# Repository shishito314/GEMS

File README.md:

# GEMS - Glovebox Environmental Monitoring System

## Table of Contents

- [Overview](#overview)
- [Instructions For Use](#instructions-for-use)
  - [Changing Display I2C Addresses](#changing-display-i2c-addresses)
  - [Binding Arduino MAC Addresses](#binding-arduino-mac-addresses)
  - [Python Configuration](#python-configuration)
  - [Adding Sensors](#adding-sensors)
  - [Changing Program Constants and Parameters](#changing-program-constants-and-parameters)
- [How GEMS works](#how-gems-works)
  - [Hardware](#hardware)
    - [Bill Of Materials](https://docs.google.com/spreadsheets/d/1ikpGfJ6LjHaBAVGgCHs3OJ50SzMK_VNal6e07bsFQgU/edit?usp=sharing)
    - [Wifi Communications](#wifi-communications)
    - [Sensor Measurement](#sensor-measurement)
  - [Software](#software)
    - [Python Overview](#python-overview)
    - [Arduino Code Overview](#arduino-code-overview)
    - [Technical Details](#technical-details)
      - [Wifi & Caching](#wifi--caching)
      - [Smoothing](#smoothing)
      - [Behavior on Disconnect](#behavior-on-disconnect)
- [Known Issues and Limitations](#known-issues-and-limitations)
- [Links](#links)

## Overview

Here's the basic idea of the GEMS system in it's current implementation:

There are two arduino boards, one inside and one outside the glovebox. The one inside is optional and connects to a temperature sensor. The one outside is part of a unit that connects to an oxygen sensor, a water/humidity sensor, and three displays (one to display each sensor measurement).

When the loop.py program is run on a computer connected to the GEMS router network, it will periodically send HTTP requests to the arduinos, which are effectively hosting servers. When it sends the request, the arduino will respond with the current sensor measurement (in the form of an HTML webpage). When it gets the measurements, the computer will log them in a file.

Then, with the current measurements, the computer will decide what should be displayed. With another HTTP request, it will send that information to the arduino with the displays, which will update the displays accordingly. Then, on the next cycle, the computer will run that entire process again, and so on.

## Instructions For Use

Here are instructions for the full setup process:

1. Install desired sensors on glovebox
2. Connect computer to router network with USB Wifi adapter (here using an auxiliary wifi adapter to retain internet access, since the local router isn't connected to the internet). You may need to install the driver from the [TP-Link download center](https://www.tp-link.com/us/support/download/) (T3U Plus is the device).
3. Set up router in lab with the given instructions. (No need for WAN/Internet, so you can skip it). Make sure router is on and network is available.
4. Optionally, install [git](https://git-scm.com/install/) on the lab computer. This will allow for easier updates if changes are made to the GEMS github.
5. If using git, clone the GEMS repository into the preferred filesystem location. On Mac and Windows, You can use the commands `cd your_folder_path` and then `git clone https://github.com/shishito314/GEMS.git`. You may need to sign in to your github.
6. If not using git, you can download the repository manually (e.g. via zip)
7. Install [Python](https://www.python.org/downloads/) on lab computer (the latest stable (non pre-release) version of Python 3 should work) You can verify that the install worked by running `python --version` in the command line.
8. Acquire or construct physical GEMS unit with arduino, PCB, displays, and box. You will need:
   - PCB soldered with all components
   - Displays soldered together ([Adafruit guide here](https://learn.adafruit.com/adafruit-7-segment-led-featherwings/overview))
   - Displays soldered with correct I2C addresses ([explanation here](#changing-display-i2c-addresses))
   - Displays plugged into header pins on PCB
   - Arduino connected to header pins on PCB
   - Box screwed together
9. Install [Arduino IDE](https://www.arduino.cc/en/software/), either on a personal or lab computer. It's only needed for setup to upload code to the arduinos.
10. Within Arduino IDE, go to the board manager and install the package for arduino megaAVR boards (like the Uno Wifi Rev2)
11. Using the Library manager, install WiFiNINA and the Adafruit LED Backpack library, including all dependencies.
12. Open the desired arduino sketch (.ino) in Arduino IDE and go to config.h. Edit NETWORK_SSID and NETWORK_PASS to be correct for the room router. Save the file.
13. Upload the code using a printer cable (USB-B) with data capability (some only transmit power). When you plug in the arduino, click the dropdown in the top left and select the board, then click upload (right arrow icon). If the arduino doesn't appear in the dropdown, there's a chance that the cable doesn't transmit data or that you need to cycle power to the arduino.
14. With arduino plugged in, open (or close and reopen) the serial monitor with the button in the top right to verify that it's working. You should see a couple prints to the serial monitor and after ~10s, the arduino should connect to the router and print out the IP address it was assigned.
15. Keeping the arduino plugged in (so we know the current IP address), bind the arduino MAC Address to the desired IP Address ([guide here](#binding-arduino-mac-adresses))
16. Restart arduino (you can close and reopen the serial monitor) and verify that it gets the desired IP address after network connection.
17. Connect the GEMS unit to the sensors via screw terminals and leads. Then using the wall mounted power adapter, plug in the PCB (not the arduino) to power. The PCB barrel jack is on the left side of the box, and the arduino's barrel jack (which can't handle this voltage) is on the top. Turn the unit on with the rocker switch (on = left down). The displays should come on after a few seconds.
18. On the lab computer, go to the command line and run `pip install matplotlib`. Alternatively you can use the environment.yml file and conda if you have it installed (otherwise probably overkill).
19. Edit the config.txt file in the Python subfolder. ([guide here](#python-configuration))
20. Run loop.py by double clicking in the file explorer or from the command line. If the program is successful, you should see a glovebox-named folder with sensor data pop up in the Python subfolder after a little while.
21. After you get some data, you can check on it by running gui.py
22. For optional temperature support, plug in a thermocouple to an arduino and go through a similar process to the other arduino:
    - Download the Adafruit MAX6675 Library and upload the temperature sketch to the arduino (again need to change network info in config.h).
    - Bind the arduino MAC Address to the desired IP address
    - Edit config.txt in the python subfolder to account for the temperature arduino
    - After changing config.txt, rerun loop.py to apply changes.
23. You're all set! Thanks for using GEMS.

### Changing Display I2C Addresses

The seven segment displays communicate with the arduino via the I2C protocol, which requires each device to have a unique address. Luckily, we can change the address from the default 0x70 by soldering on the display board.

There are 3 address jumpers on the display board (the pairs of solder pads marked A0, A1, A2). Each jumper represents a bit: 1, 2, and 4 for A0, A1, and A2 respectively. The final address is 0x70 + the sum of all the bits. For example, to get the address 0x73, you would solder together the A0 pads and A1 pads (70 + 1 + 2 = 73).

You can find the Adafruit guide on changing the I2C addresses [here](https://learn.adafruit.com/adafruit-7-segment-led-featherwings/pinouts#changing-addresses-1805676)

In the current GEMS arduino code, the displays are set up as follows:

- Temperature display → 0x70 (no jumpers)
- Oxygen display → 0x71 (A0 soldered)
- Water display → 0x72 (A1 soldered)

### Binding Arduino MAC Adresses

1. Connect to the router network and go to the configuration page at [http://tplinkwifi.net/](http://tplinkwifi.net/) (Note the http, not https). If your computer is connected to internet, you may need to try searching the router IP address directly (solution 2).
2. Sign in with admin password posted on the router
3. Depending on how old your router is, there are different versions of the web page. Either:
   1. Click "Advanced," "Network," and "DHCP Server" (new version)
   2. Click "DHCP" on the left, then "Address Reservation" (old version)
4. With the new version of the webpage, you should be able to scroll down and see the currently connected clients. If you know the IP address of the arduino from the serial monitor output, you can use that to identify its MAC address.
5. Alternatively, you can get the arduino MAC address by temporarily uploading the getMacAddress sketch and reading the output from the serial monitor. You'll need to change the "ssid" and "pass" in the code to the network name and password. WARNING: depending on your library version, the printed MAC address might actually have the pairs of letters/numbers backwards (e.g. AB:CD:EF:12:34:56 is actually 56:34:12:EF:CD:AB).
6. Add a new address reservation line on the router configuration page, and input the MAC Address with the desired IP Address. You can use `198.162.0.11_` as a possible naming scheme, just varying the last digit.
7. If on the old web page, switch address reservation to "Enable"

### Python Configuration

To configure the software for certain gloveboxes, arduinos, and sensors, use the config.txt file in the Python subfolder. If you downloaded or cloned the GEMS repository, an example is provided by default.
Here's the format for a config file:

```
Glovebox: [Name]
Arduino: IP: [IP Adress] Display: [True/False] Sensors: [Sensor1 Sensor2...]
Arduino: IP: [IP Adress] Display: [True/False] Sensors: [Sensor1 Sensor2...]
Glovebox: [Name]
[Arduinos...]
...
```

Here's an example of a config file following that format:

```
Glovebox: pluto
Arduino: IP: 192.168.0.110 Display: True Sensors: Oxy Water
Arduino: IP: 192.168.0.111 Display: False Sensors: Temp
Glovebox: neptune
Arduino: IP: 192.168.0.112 Display: True Sensors: Oxy
Arduino: IP: 192.168.0.113 Display: False Sensors: Temp
```

IMPORTANT: Capitalization and the colons after words are mandatory.

### Adding Sensors:

This section is for adding new sensor types in software (e.g. if you wanted to add functionality for a pressure sensor). Each sensor has a class in gems.py extended from the base Sensor class. To create your own, make a class extended from the base Sensor class and define the addVal and getLog methods for your sensor. It might look something like the following:

```python
class NewSensor(Sensor):
  flag = NEW_SENSOR_FLAG # Flag to be used in HTTP communications and logging
  datatype = float # The datatype of the sensor measurements (e.g. float)

  def __init__(self):
    super().__init__()
    self.lastValue = None

  def getLog(self):
    try:
      return str(round(self.lastValue, 3))
    except:
      try:
        return self.lastValue
      except:
        return "Error"

  def getDisplay(self):
    try:
      return str(round(self.lastValue, 3))
    except:
      if (self.lastValue):
        return self.lastValue
      else:
        return DISPLAY_ERROR_MESSAGE

  def addVal(self, val, time):
    self.lastValue = val
```

You can also look at the sensor classes already implemented for some examples.

After making the sensor, class, add a corresponding configuration flag and sensor class to the "SENSOR_CONFIG_FLAG_TO_CLASS" dictionary in the "Set Up Class Instances From Config" section of gems.py. You'll also need to define a flag, (whatever you'd put in place of "NEW_SENSOR_FLAG" in the above example), and add that flag to the LOG_FLAGS list in the constants section of gems.py. It'll get used for parsing through log files with the data utilities.

### Changing Program Constants and Parameters

When changing constants in the programs, it is important to note that variables labeled "MUST MATCH ARDUINO" or "MUST MATCH PYTHON" must be the same in both programs. They should be at the top of gems.py or in the config.h file in the arduino sketches.

## How GEMS works

### Hardware

[Bill Of Materials]([https://docs.google.com/spreadsheets/d/1ikpGfJ6LjHaBAVGgCHs3OJ50SzMK_VNal6e07bsFQgU/edit?usp=sharing])

#### Wifi Communications

Uses:

- Computer with python 3
- Router
- Wifi adapter
- Arduinos

The wifi adapter connects the computer to the router network, and the router network connects the computer and arduinos together. The arduinos are hosting a server, which the computer can send a request to by sending it to "http://" followed by the arduino IP address. The arduinos must have an IP address that doesn't change, so we use the MAC address binding on the router to keep the IP address constant.

#### Sensor Measurement

The oxygen and moisture sensors are 4-20 milliamp loop sensors, with a power lead (24V) and an output (goes across a resistor to GND) The sensor regulates the current on the output to be between 4 and 20 milliamps, and the current corresponds to the sensor measurement.

Since the arduinos can't measure current directly, we instead measure the voltage drop across a known resistor and calculate the current

Since it is important to know the resistance of the resistor accurately, there is a 0.1% tolerance resistor with 25ppm per degree C temperature coefficient.

There are some other pieces of hardware that address a few problems:

- Capacitor: There is a 10 uF capacitor running in parrallel with the resistor. It acts as a low pass filter to reduce some of the noise (15.5KHz sine wave) that had been a prior issue
- Voltage Reference: The built in arduino voltage references weren't accurate enough for the desired specs, so we use an external 4.5V reference.

### Software

#### Python Overview

- [loop.py](./Python/loop.py): The update loop that sends http requests and logs data. It's an infinite loop that must be stopped by closing the python terminal.
- [gems.py](./Python/gems.py): All the architecture and setup for the GEMS system. Parses config.txt upon import.
- [data.py](./Python/data.py): Utility functions for extracting and plotting data from GEMS log files.
- [gui.py](./Python/gui.py): Runs the GEMS GUI (graphical user interface). You can use it to check up on the GEMS system and measurements.

#### Arduino Code Overview

- [oxyWaterDisplay](./Arduino/oxyWaterDisplay/): Handles sensor measurements for the oxygen and dewpoint sensors, wifi communication, and readouts.
- [temp](./Arduino/temp/): Similar to the oxyWaterDisplay sketch, but stripped down for only the temperature sensor and wifi, no displays.
- [getMacAddress.ino](./Arduino/getMacAddress.ino): Connects to the router wifi network, then prints the arduino MAC address in the Serial Monitor.

#### Technical Details

##### Wifi & Caching

The following wifi protocol and caching system are designed to prevent data from being lost, even if HTTP requests or responses are missed:

The arduino has a cache that stores the logs to send to the lab computer. Conceptually, the arduino cache has two parts. The "old" part of the cache consists of data that has already been sent, but the arduino isn't sure that the computer received it. The "new" part of the cache is data that has not yet been sent. (In practice, for memory management, I use an array with flexible start/end indices and wraparound behavior).

Every [CACHE_CYCLE_DELAY] milliseconds, the arduino will add a new log to the new part of the cache. When the arduino receives a request from the lab computer, the request comes with a note that says whether or not the computer got the previous request. If so, the arduino will clear the old cache to avoid sending repeat data. Then, the arduino will send the cache via wifi to the computer, and the entire cache will be labeled as "old" (since the data was sent). If the computer did not receive the previous request, the old cache will not be cleared and therefore the data will be resent.

However, it is still possible that repeat data will be sent, for example if the python program is stopped and restarted. The python program will have written the data in the file, but whether it received the last request defaults to "no" on startup. Therefore, on the first request, the python program won't tell the arduino to clear the old cache, and the old cache will be sent again as a repeat log.

A timestamp system is there to prevent this log duplication. Every log that the arduino makes is labeled with the arduino clock value (in milliseconds) at the time of measurement. When the computer receives the logs, it will save the timestamps of those logs inside a hidden file that persists after the python program is stopped. The next time that the computer gets logs, it will check to make sure that the timestamps for those logs do not line up with the ones in the hidden file. That way, the computer can avoid both missing data and repeating measurements in the log files.

##### Smoothing

Currently, the arduino takes measurements from the analog pins every loop cycle. It adds those measurements to an array for smoothing, and gets rid of the oldest measurement in the array. However, those measurements are not a single reading from the analog pin, but rather many readings averaged out to a single value. That way, a higher smoothing value could be achieved with the same amount of memory than by taking single measurements.

For example, with 30 16-byte-integers worth of memory, you could either have an array with 30 measurements, or you could have an array of 15 averages of 15 measurements each. Therefore, the effective smoothing is with 225 values, not just 30.

Also, the readings can be taken close together, since they are taken right after each other instead of waiting for another cycle of the arduino loop function.

##### Behavior on Disconnect

When the display arduino gets disconnected, it will calculate the oxygen and humidity values locally and display those. It won't display the temperature, instead showing "dISC" for disconnected. It will keep caching new data for when it reconnects, though.

## Known Issues and Limitations

- The arduino clock isn't perfectly accurate, so after a while there may be slightly more or less logs than expected
- Arduino timestamps leave minuscule probability of missing or repeating a log
- Can't support multiple sensors of the same type on one glovebox (because it can't differentiate flags)
- Logging untested with daylight savings time
- Non-flexible file structure
- Some computers may stop sending wifi requests when the computer screen turns off
- No timeout in arduino sketch if client doesn't disconnect

## Links

[Google Drive Folder](https://drive.google.com/drive/folders/1qjnQDnakjW4T2VA_t_dMa19qW6lmA9qH?usp=sharing)

[Full Bill Of Materials](https://docs.google.com/spreadsheets/d/1ikpGfJ6LjHaBAVGgCHs3OJ50SzMK_VNal6e07bsFQgU/edit?usp=sharing)

[Desmos Graph For Spec Calculations](https://www.desmos.com/calculator/oaaztaypr6)

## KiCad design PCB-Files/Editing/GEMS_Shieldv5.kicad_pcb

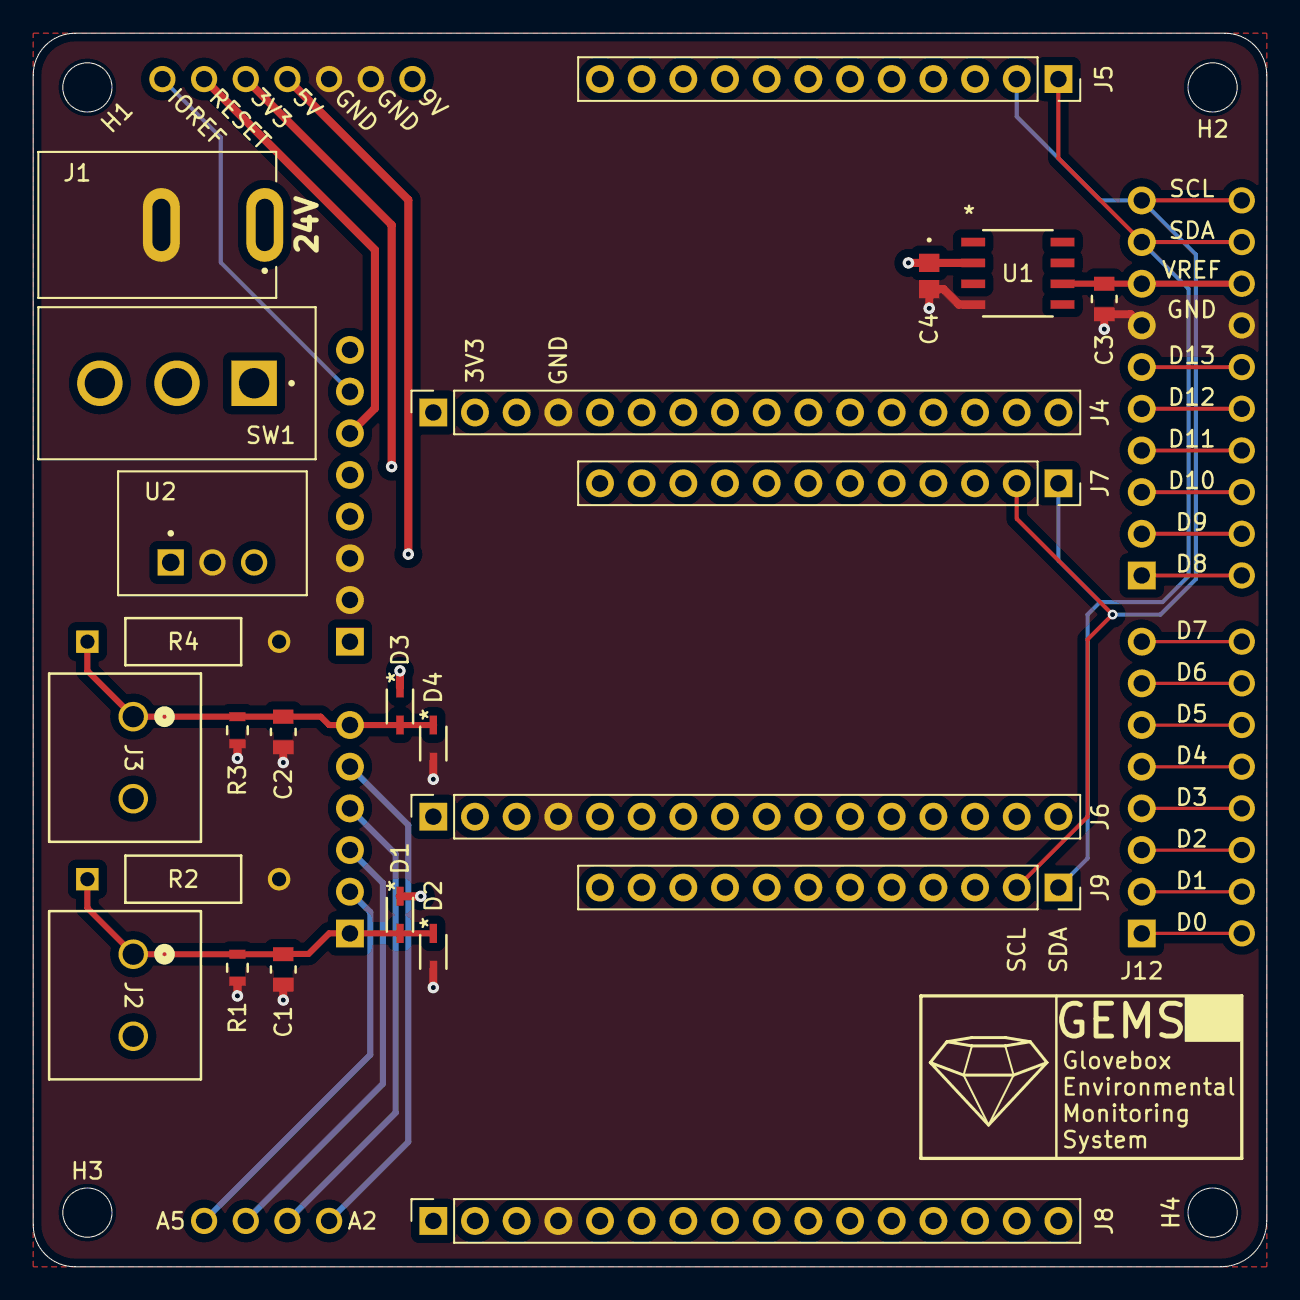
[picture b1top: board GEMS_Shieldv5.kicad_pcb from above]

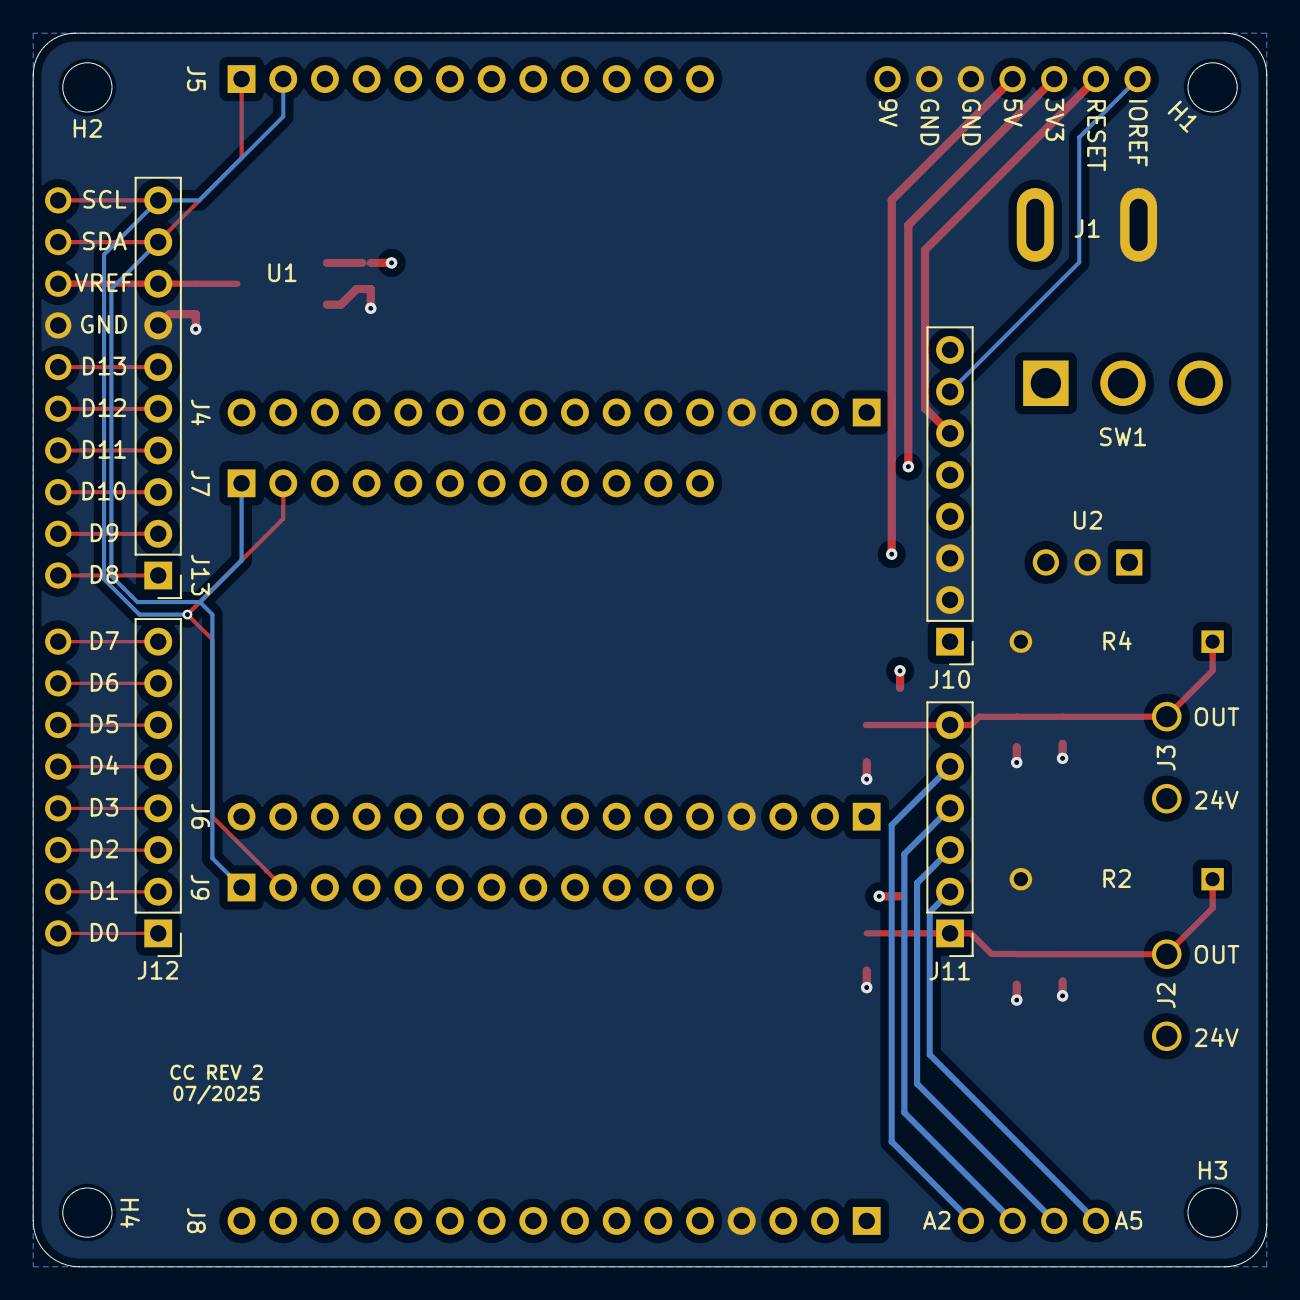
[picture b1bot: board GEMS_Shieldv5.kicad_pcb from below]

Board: 4 copper layers, 75.2 x 75.2 mm, 61 parts (4 on the bottom side), 10 nets.

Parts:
A1: Arduino_UNO_R3; Arduino_Wifi_Drawing
C1, C2: C; CL21A106KOQNNNE_10uF
C3: C; CL21B105KBFNNNE_1uF
C4: C; CAP_KGM21_KAV
D1, D2, D3, D4: D; CR_SOD323_MCC
H1, H2, H3, H4: MountingHole
J1: Barrel_Jack; CUI_PJ-037A
J2, J3: Screw_Terminal_01x02; CONN_1935161_PXC
J4, J6, J8: Conn_01x16_Socket; PinSocket_1x16_P2.54mm_Vertical
J5, J7, J9: Conn_01x12_Socket; PinSocket_1x12_P2.54mm_Vertical
J10, J12: Conn_01x08_Pin; PinHeader_1x08_P2.54mm_Vertical
J11: Conn_01x06_Pin; PinHeader_1x06_P2.54mm_Vertical
J13: Conn_01x10_Pin; PinHeader_1x10_P2.54mm_Vertical
J14, J15, J16, J17, J18, J19, J20, J21, J22, J23, J24, J25, J26, J27, J28, J29, J30, J31, J32, J34, J35, J36, J37, J38, J39, J40, J41, J42: Conn_01x01_Socket; THT_Connection
R1, R3: R; RES_0816_SUS
R2, R4: R; YAG_MF25_YAG
SW1: SW_SPDT; SW_300SP1J1BLKM2QE
U1: MAX6167AESA+; 21-0041B_8_MXM
U2: CONV_R-78K9.0-0.5

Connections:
+3.3V: J4.2, J6.2, J8.2, J10.5, J18.1
+5V: D1.1 (K), D3.1 (K), J10.4, J17.1
+9V: C4.1, J10.1, J14.1, U1.2 (IN), U2.3 (9V)
+24V: J1.1, J2.2, J3.2, SW1.1 (A), SW1.2 (B), U2.1 (24V)
GND: C1.2, C2.2, C3.2, C4.2, D2.2 (A), D4.2 (A), J1.2, J4.4, J6.4, J8.4, J10.2, J10.3, J13.7, J15.1, J16.1, J40.1, R1.2, R2.2, R3.2, R4.2, U1.4 (GND), U2.2 (GND)
unnamed: C1.1, D1.2 (A), D2.1 (K), J2.1, J11.1, R1.1, R2.1
unnamed: C2.1, D3.2 (A), D4.1 (K), J3.1, J11.6, R3.1, R4.1
unnamed: C3.1, J13.8, U1.6 (OUT)
unnamed: J5.1, J7.1, J9.1, J13.9, J41.1
unnamed: J5.2, J7.2, J9.2, J13.10, J42.1

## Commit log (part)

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2023-09-28 Added display testing and files from google drive
2023-09-28 Added files for Bluetooth testing
2023-11-19 Create NanoGEMSv2
2023-11-19 Create UnoGEMSv2
2023-11-21 Rename UnoGEMSv2 to UnoGEMSv2.ino
2023-11-21 Rename NanoGEMSv2 to NanoGEMSv2.ino
2024-06-13 moved to archive
2024-06-13 move to archive
2024-06-13 Rename httpConnect.py to http-connect.py
2024-06-13 Rename ThermoWifiTest/ThermoWifiTest.ino to ThermoWifiTest.ino
2024-08-09 Rename ThermoWifiTest.ino to Archive/ThermoWifiTest.ino
2024-08-09 Rename http-connect.py to Archive/http-connect.py
2024-08-22 Rename now.py to Python/now.py
2024-08-22 Rename data.py to Python/data.py
2024-08-22 Rename gui.py to Python/gui.py
2024-08-22 Rename loop.py to Python/loop.py
2024-08-22 Rename OxyWaterDisplay.ino to Arduino/OxyWaterDisplay.ino
2024-08-22 Rename Temp.ino to Arduino/Temp.ino
2024-08-22 Rename GEMS_Shieldv3-all.pos to PCB-Files/Ordering/GEMS_Shieldv3-all.pos
2024-08-22 Rename PCB-Files/fp-info-cache to PCB-Files/Editing/fp-info-cache
2024-08-22 Rename PCB-Files/Editing/21-0041B_8_MXM.kicad_mod to PCB-Files/Editing/GEMS_Custom.pretty/21-0041B_8_MXM.kicad_mod
2024-08-22 Rename OxyWaterDisplay.ino to oxyWaterDisplay.ino
2024-08-22 Rename Temp.ino to temp.ino
2024-08-22 Rename GetMacAddress.ino to getMacAddress.ino
2024-08-26 Rename Full Assembly.step to CAD-Files/Full Assembly.step
2025-07-17 Add anaconda environment.yml
2025-07-17 updated to v12 version
2025-07-18 updated comments and readability
2025-07-22 added gitignore
2025-07-23 Fixed Python and updated Arduino caching system
2025-07-30 reorganized GUI + structure changes
2025-07-30 PCB changes
2025-07-30 Got rid of __pycache__
2025-08-01 data and gui changes
2025-08-01 remove testing files
2025-08-01 remove pycache
2025-08-04 change log tab in gui
2025-08-05 added getMeasurementNearTime functions
2025-08-06 Added daylight savings time safety
2025-08-06 changed plotting
2025-08-06 updated to work on lab computer
2025-08-07 added graph tab in GUI
2025-08-18 GUI changes
2025-08-19 CAD files and fixed Arduino code
